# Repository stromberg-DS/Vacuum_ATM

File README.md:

# Vacuum_ATM
Automatically reward the first person who vacuums the floor.

This is a project that tracks the dust levels in your house and tells you when to vacuum. A Photon 2 microcontroller detects when the vacuum is removed/replaced. Meanwhile a separate Photon 2 mounted inside a toy vending machine tracks if you have vacuumed for long enough to get a reward. If you have vacuumed long enough, you can turn the crank and get a plastic capsule filled with whatever (money, candy, etc).

## Directory

**Vacuum_ATM** - This folder contains the code for the dispensing side of the system.

**Vacuum_Status** - This folder contains the code for the photon that senses the presence of the vacuum.

**3D_Models** - Models to print out to get everything to work.

**Cut_Files** - Files to cut on a CNC router or laser cutter.

**Wiring Diagram** - Images of the wiring of both the Vacuum ATM and the Vacuum Status Photons.

**Testing** - Where I did all of my initial R&D. Actually I'm kind of embarassed that you would even want to look in here. Go back up to 3D_models. This is not a good look for you.

More information can be found at [my Hackster.io writeup](https://www.hackster.io/blotlat/vacuum-atm-a74ef9)

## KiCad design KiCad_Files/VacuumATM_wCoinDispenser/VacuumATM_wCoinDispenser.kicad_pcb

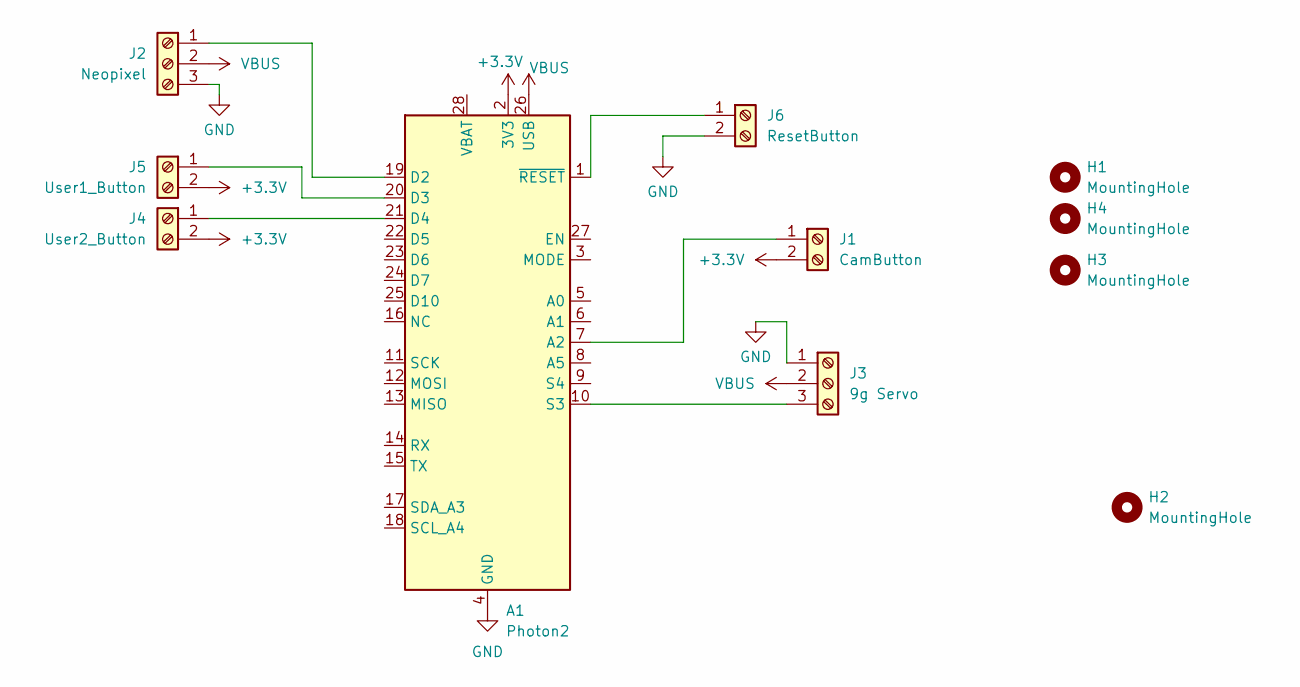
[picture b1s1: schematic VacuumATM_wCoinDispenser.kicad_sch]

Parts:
A1: Photon2
H1, H2, H3, H4: MountingHole; MountingHole_2.5mm_Pad
J1: CamButton; TerminalBlock_Phoenix_MPT-0,5-2-2.54_1x02_P2.54mm_Horizontal
J2: Neopixel; TerminalBlock_Phoenix_MPT-0,5-3-2.54_1x03_P2.54mm_Horizontal
J3: 9g Servo; TerminalBlock_Phoenix_MPT-0,5-3-2.54_1x03_P2.54mm_Horizontal
J4: User2_Button; TerminalBlock_Phoenix_MPT-0,5-2-2.54_1x02_P2.54mm_Horizontal
J5: User1_Button; TerminalBlock_Phoenix_MPT-0,5-2-2.54_1x02_P2.54mm_Horizontal
J6: ResetButton; TerminalBlock_Phoenix_MPT-0,5-2-2.54_1x02_P2.54mm_Horizontal

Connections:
+3.3V: A1.2 (3V3), J1.2, J4.2, J5.2
GND: A1.4 (GND), J2.3, J3.1, J6.2
unnamed: A1.7 (A2), J1.1
unnamed: A1.19 (D2), J2.1
unnamed: A1.20 (D3), J5.1
unnamed: A1.21 (D4), J4.1
unnamed: A1.10 (S3), J3.3
unnamed: A1.1 (~RESET), J6.1
VBUS: A1.26 (USB), J2.2, J3.2

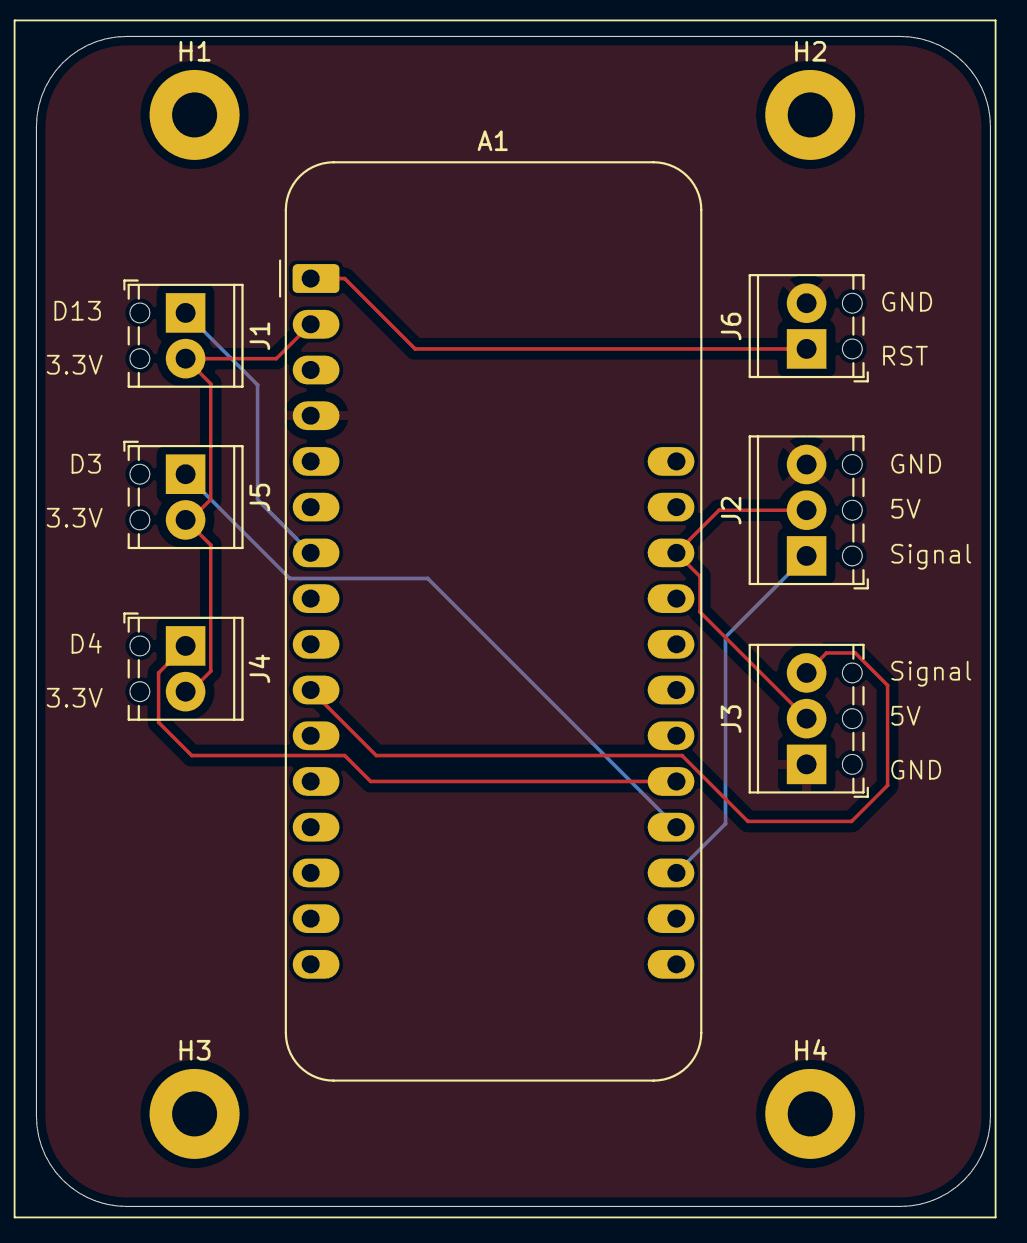
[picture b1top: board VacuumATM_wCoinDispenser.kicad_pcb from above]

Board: 2 copper layers, 53.0 x 65.0 mm, 11 parts (0 on the bottom side), 9 nets.

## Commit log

2024-04-19 Updated gitignore, added folders
2024-04-19 Added flowchart
2024-04-19 Threaded dust sensor working. Updating to Adafruit
2024-04-19 Testing fingerprint sensor, no luck yet
2024-04-21 Testing fingerprint code
2024-04-21 Pull dust info from plant. Publish total dust amount.
2024-04-21 Prep for saving dust in EEPROM
2024-04-22 Saving dust data to EEPROM
2024-04-22 Total dust level remaining through resets
2024-04-22 Neopixels working
2024-04-22 Added button class
2024-04-22 Added a vacuum-simulator button
2024-04-22 Added button released to button class
2024-04-22 Added nul to gitignore
2024-04-23 Fixed button logic
2024-04-23 Logic works through once. Lights working well, non-blocking
2024-04-26 Added time difference test
2024-04-26 Wait for cloud to connect to avoid negative times
2024-04-26 Added questions for professor
2024-04-26 Added main program
2024-04-26 Vacuum timer works/resets
2024-04-26 lunch break!
2024-04-26 Added basic version of vacuum logic
2024-04-26 End of day push
2024-04-28 Added rubric for reference
2024-04-28 Updated Project Plan
2024-04-29 Servo working in code, added CAD files
2024-04-29 Added KiCad files
2024-05-03 Shrank hole cover
2024-05-03 Testing alternate print orientation for shaft collar
2024-05-03 Made a mount for hall effect sensor.
2024-05-03 Removed nonfunctional holes for servo.
2024-05-03 Added alternate tie down for hall effect sesor
2024-05-03 Added servo mount file
2024-05-03 Combining servo and hall sensor
2024-05-05 Hall sensor opens servo after vacuum is returned
2024-05-05 Swapping hall effect sensor for micro switch
2024-05-05 Made cam larger, smaller fillets
2024-05-05 Servo only opens 1x per vacuuming now
2024-05-05 Need more extreme cam profile
2024-05-06 Added 2nd Photon to just monitor the vacuum charger
2024-05-06 Sending current vac state and time the state changed to adafruit as a string
2024-05-06 Changed LED to breathing
2024-05-06 Turn off other onboard LEDs
2024-05-06 Trying to get vacuum status from other Photon
2024-05-06 Updated vac button pin
2024-05-07 Added ping function to keep MQTT connection alive
2024-05-07 Fiddlig around to parse out incoming data
2024-05-07 Switched to sending vac status only
2024-05-07 Send only vacuum status
2024-05-07 Added MQTT_Ping
2024-05-07 Start tracking rising, falling edge of vacuum charging
2024-05-08 Made back wall thicker
2024-05-08 Added bottom case design for vacstatus electronics
2024-05-08 Moved charging hole offcenter
2024-05-08 Added hole to pop out breadboard
2024-05-10 Tweaked Vacuum Status case
2024-05-10 Added images of VacStatus case
2024-05-10 First display test
2024-05-10 Added a video of coin dispenser
2024-05-10 Adjusted thickness for better light diffusion, changed text
2024-05-10 Reorganizing files
2024-05-10 Getting vacuum chargin status from VacStatus Photon2 instead of from switch
2024-05-10 End of day update
2024-05-11 Added DXFs of design panels
2024-05-11 Updated Fritzing
2024-05-11 Changed units to inches, made vCarve file
2024-05-12 Added mount for LED strip.
2024-05-12 Added laser cut file for acrylic pieces
2024-05-12 Updated faceplate, toolpaths
2024-05-13 Added LED ring and strip
2024-05-14 Slightly increased width of pieces to fit better
2024-05-14 Separated LED ring and strip
2024-05-15 Added a mount for the reset button
2024-05-15 Updated display for better fit and visuals
2024-05-15 Added render
2024-05-15 Updated LEDmount location
2024-05-15 Reorganized 3D models
2024-05-15 Added images
2024-05-16 Reorganized and updated schematics
2024-05-17 Adding image
2024-05-17 Updates to KiCAD, images
2024-05-18 Redesigned PCB, made Gerber files
2024-05-20 Added Gerber files
2024-06-05 Added corrected KiCad footprint and symbol for Photon 2
2024-06-22 Updated KiCAD files
2024-06-23 Updated ring to loading bar
2024-06-24 Thickened switch cam, added set screw option.
2024-06-24 Improved LED colors and feel.
2024-07-08 Updated vacuuming time
2024-10-06 Fixed breathing LED jitter.
2024-10-06 Adjusted dust levels and vacuum times.
2024-10-12 Updated vacuuming color to something more pleasing.
2025-01-10 Added watchdog timer
2025-07-08 minor changes
2025-07-08 Added a demo button, kinda
2025-07-10 Fixed the demo button issue.
2025-07-10 Mostly working Demo Mode
2025-07-10 Reset and pause at start with demo button.
